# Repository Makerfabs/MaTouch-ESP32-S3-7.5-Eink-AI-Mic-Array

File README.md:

# MaTouch ESP32-S3 7.5 Eink AI Mic Array

## Introduction

Our MaTouch ESP32-S3 7.5-inch Quad-color E-Ink Display AI Microphone Array Development Board features a 7.5-inch quad-color e-paper display supporting black, white, red, and yellow color rendering. Based on microcapsule electrophoretic display technology, the screen drives charged pigment particles within microcapsules using electric fields, reflecting ambient light to form sharp images that deliver a natural reading experience similar to printed paper.
 
The board is powered by the ESP32-S3R8 main controller, equipped with 8 MB PSRAM and 16 MB SPI Flash. It integrates a four-microphone array and an ES7210 multi-channel audio ADC, enabling multi-channel audio capture for voice recognition, far-field sound pickup, and acoustic algorithm development. Additionally, it includes a QMI8658A six-axis inertial measurement unit providing accelerometer and gyroscope data for motion detection, orientation sensing, and interactive control. The board also features a camera, TF card slot, USB Type-C interface, lithium battery charging circuit, and reserved battery level monitoring functionality, making it ideal for application development in e-paper displays, image capture, voice interaction, and motion sensing.

Product Link: [MaTouch ESP32-S3 7.5 Eink AI Mic Array](https://www.makerfabs.com/matouch-esp32-s3-7-5-quad-color-eink-epaper.html)

Wiki Link:  [MaTouch ESP32-S3 7.5 Eink AI Mic Array](https://wiki.makerfabs.com/MaTouch%20ESP32_S3%207.5%20Eink%20AI%20Mic%20Array.html)

Example：1.[Camera_display_pic](https://github.com/Makerfabs/MaTouch-ESP32-S3-7.5-Eink-AI-Mic-Array#camera_display_pic)

2.[Voice_EPD_SD_Display](https://github.com/Makerfabs/MaTouch-ESP32-S3-7.5-Eink-AI-Mic-Array#voice_epd_sd_display)

## LCD Specs:

- PART NUMBER:KEGM075004E05
- SIZE:7.5 inch
- TYPE:Dot Matrix
- IC：JD79665
- RESOULUTION:800×480
- OUTLINE SIZE(mm):170.2×135.2×1.111
- ACTIVE SIZE(mm):163.2×97.92
- PIXEL PITCH(mm):0.204×0.204
- OPERATING TEMP:0°C ~ 40°C
- STORAGE TEMP:-25°C ~ 60°C
- CONNECTOR:24 Pin FPC
- COLOR:Black,White,Red,Yellow
- INTERFACE:SPI
- FULL REFRESH(S):20

## Features

- Controller:ESP32-S3
- Wireless:WiFi&Bluetooth 5.0
- Flash:16MB Flash
- PSRAM:8MB
- MICRO SD:Yes
- IMU:QMI8658A
- Camera:OV3660
- Microphone input:4-Microphone Array
- Audio ADC:ES7210
- USB:1*USB_NATIVE
- Arduino support:Yes

## Example

### Camera_display_pic

For details of this example, please refer to the [Wiki](https://wiki.makerfabs.com/MaTouch%20ESP32_S3%207.5%20Eink%20AI%20Mic%20Array.html#41-camera_display_pic) document.

### Voice_EPD_SD_Display

For details of this example, please refer to the [Wiki](https://wiki.makerfabs.com/MaTouch%20ESP32_S3%207.5%20Eink%20AI%20Mic%20Array.html#42-voice_epd_sd_display) document.

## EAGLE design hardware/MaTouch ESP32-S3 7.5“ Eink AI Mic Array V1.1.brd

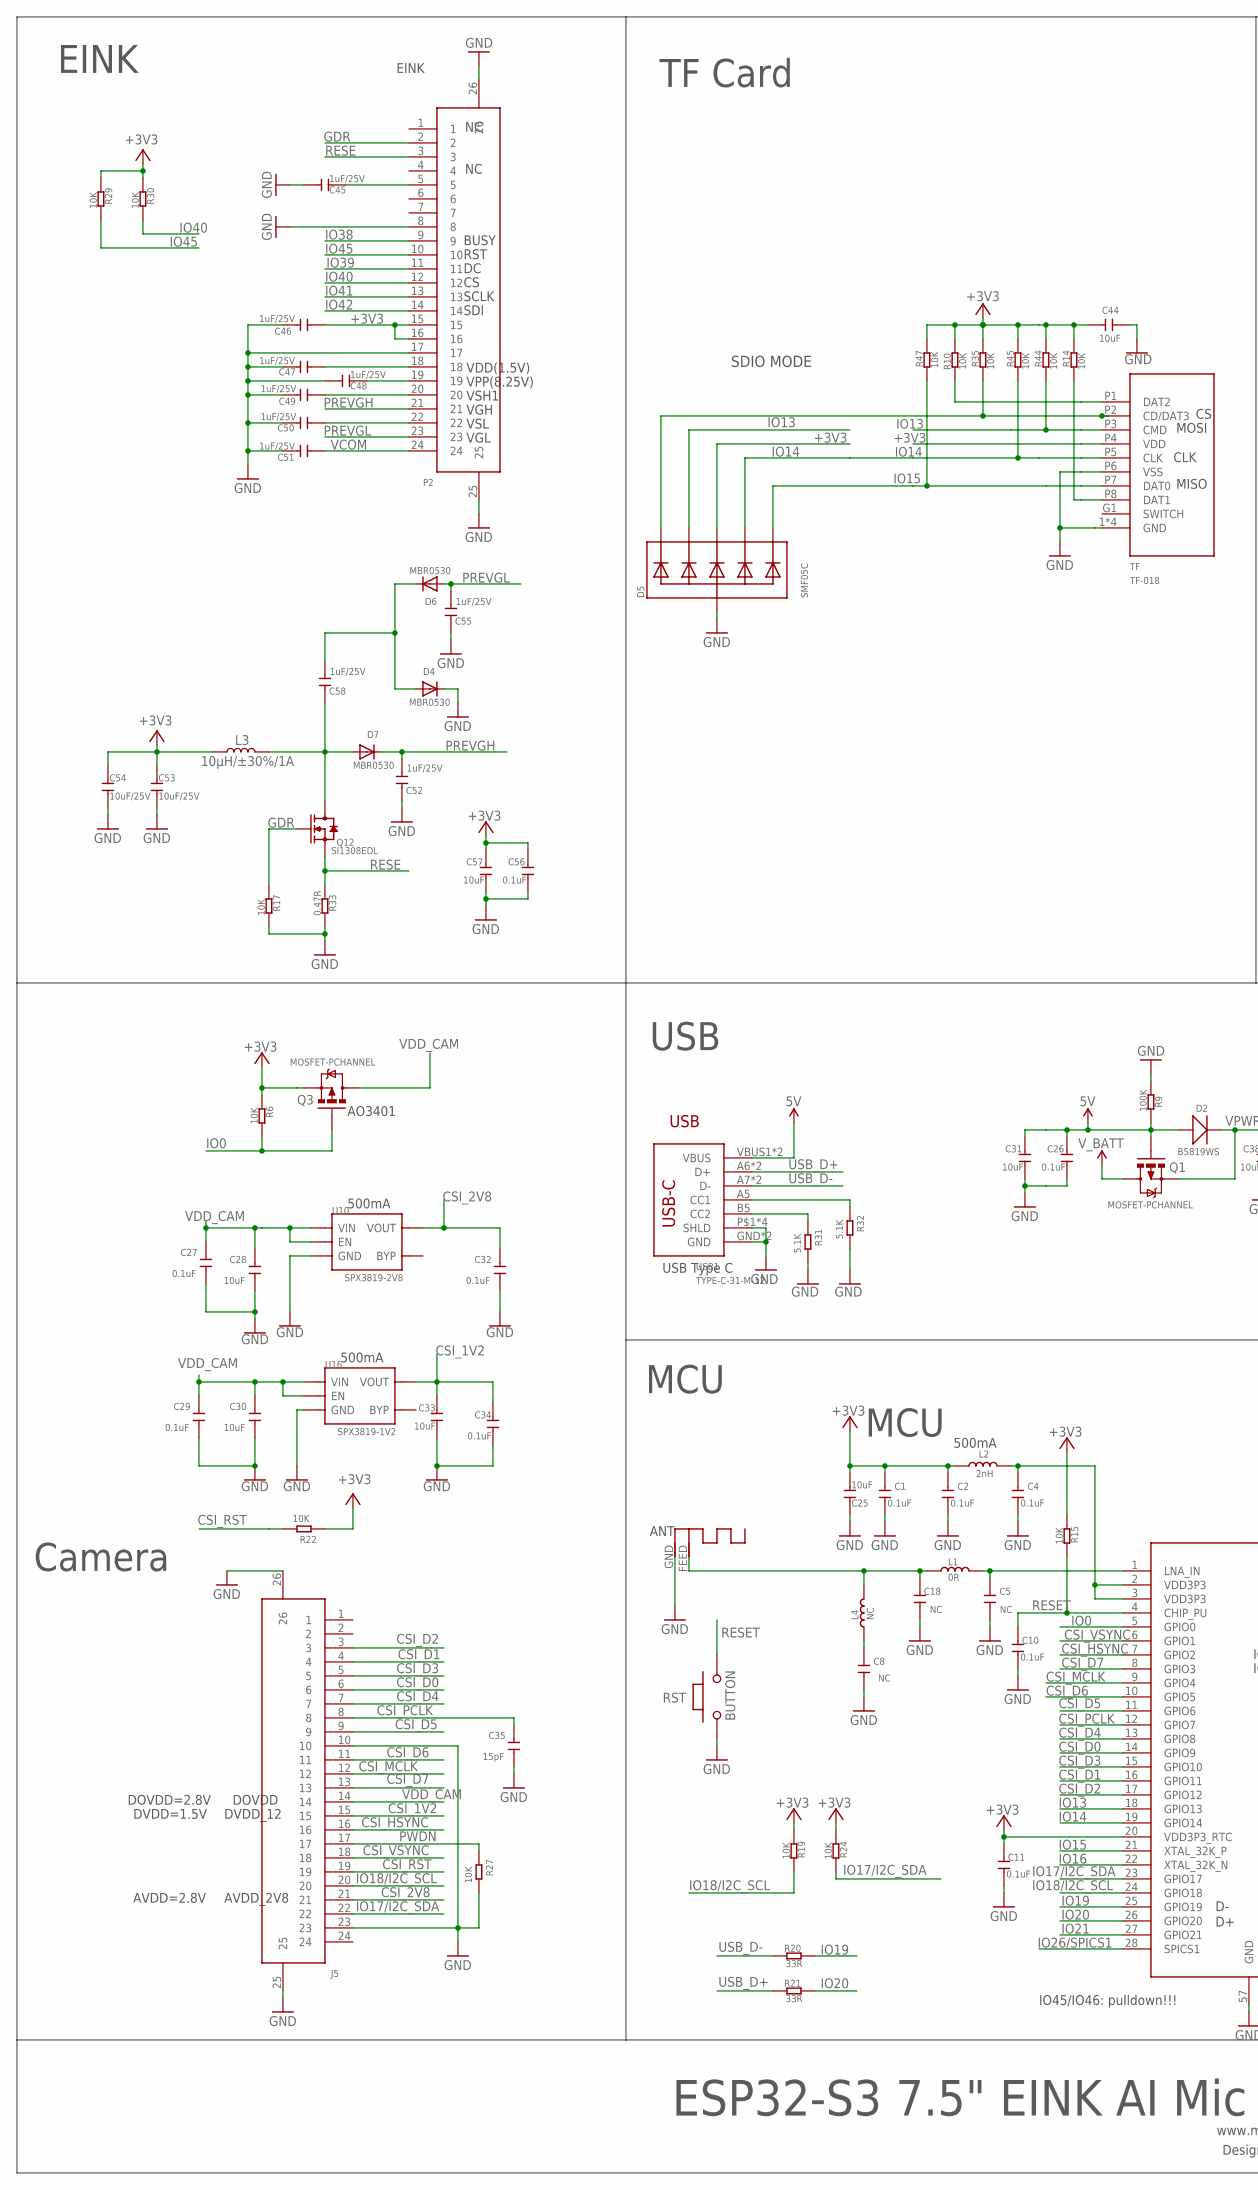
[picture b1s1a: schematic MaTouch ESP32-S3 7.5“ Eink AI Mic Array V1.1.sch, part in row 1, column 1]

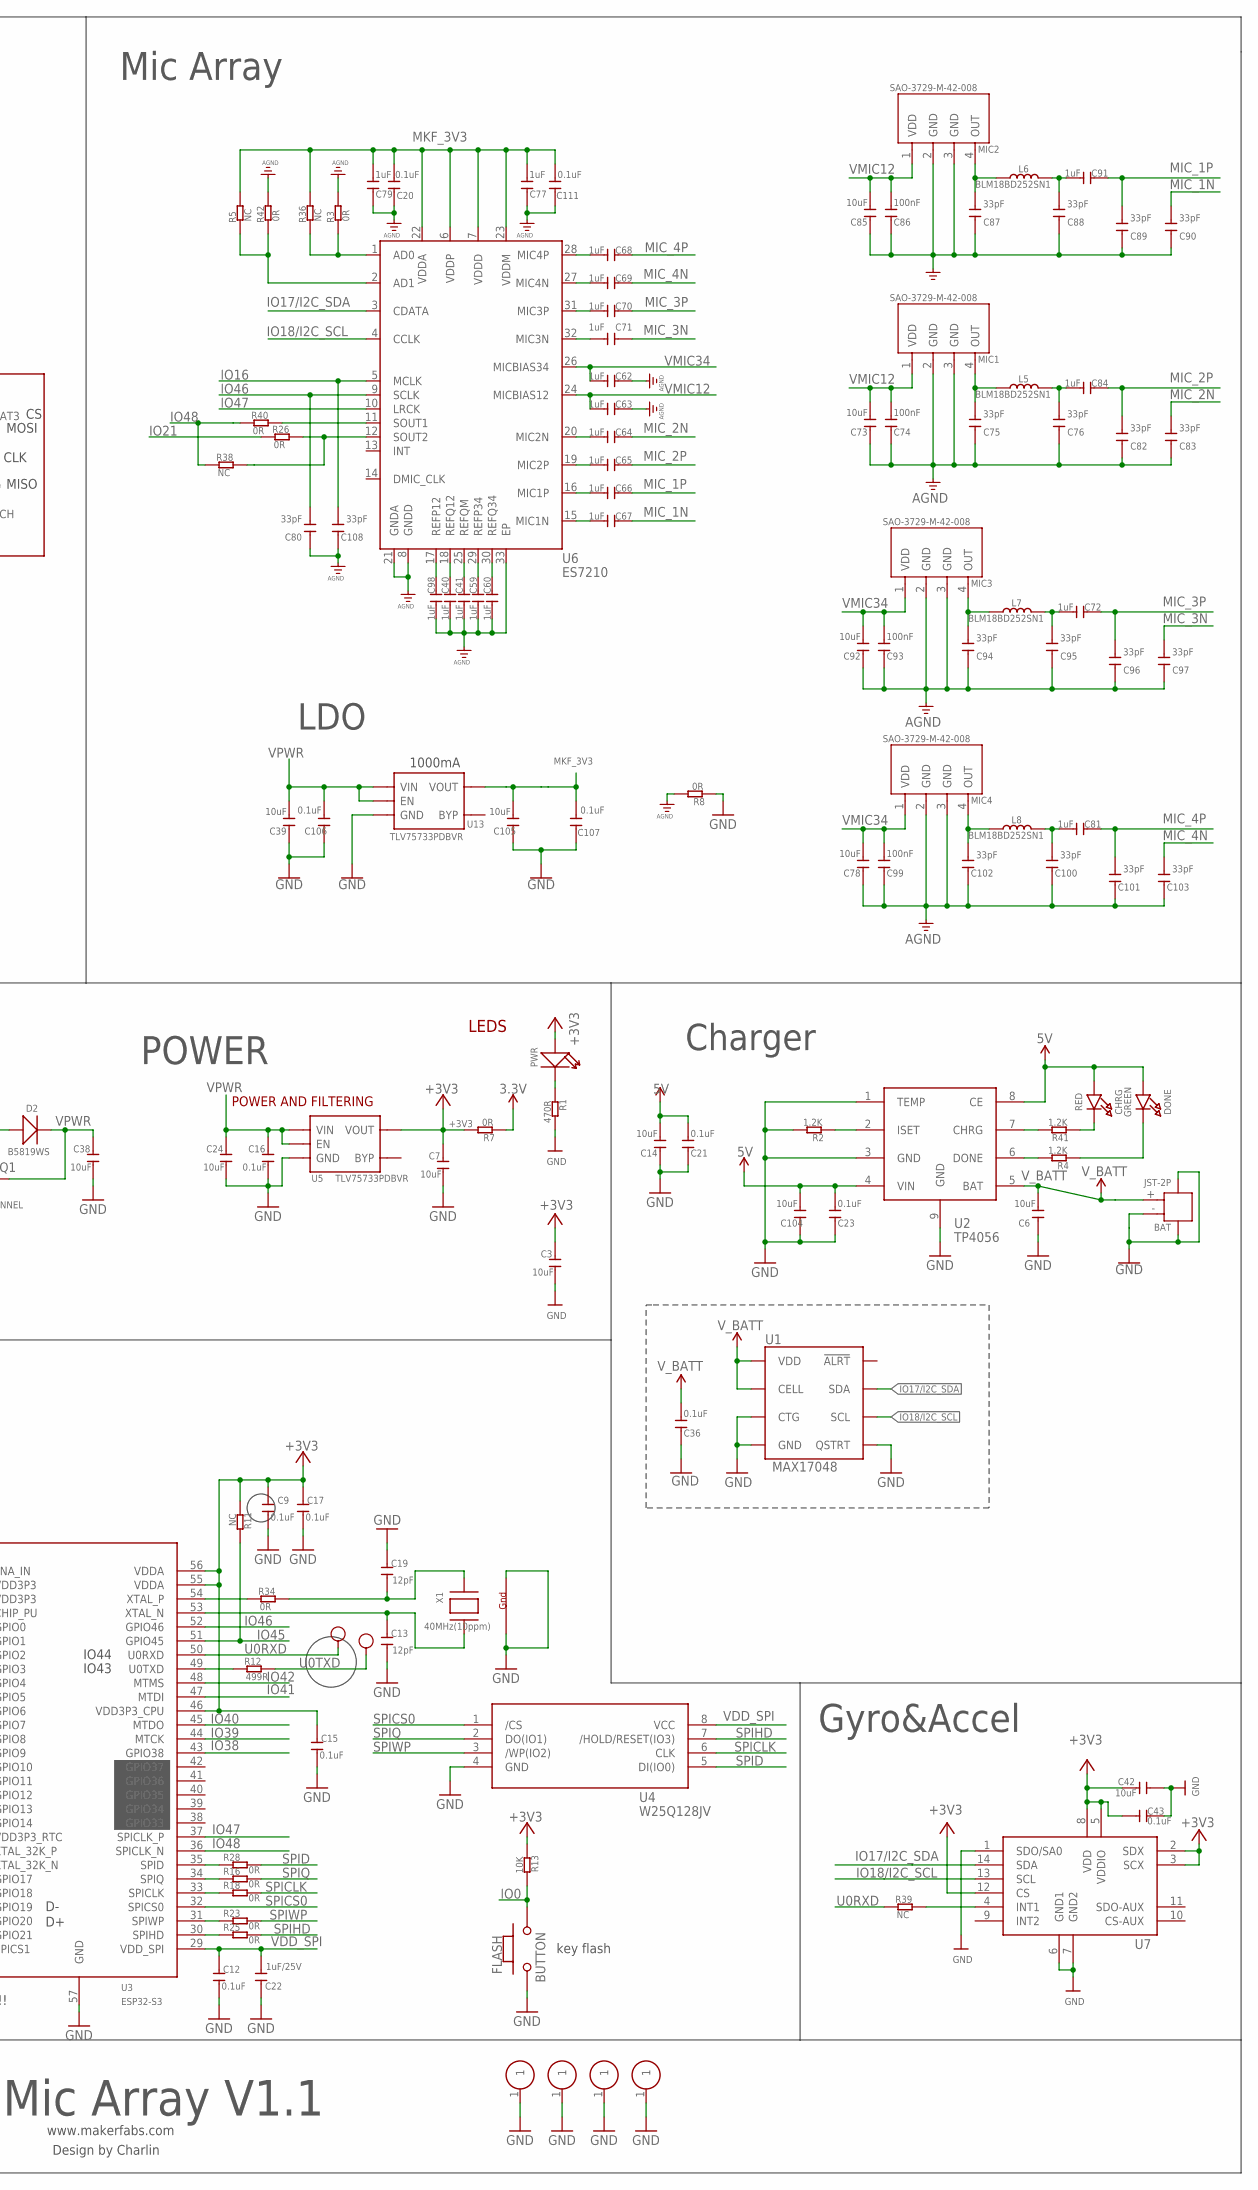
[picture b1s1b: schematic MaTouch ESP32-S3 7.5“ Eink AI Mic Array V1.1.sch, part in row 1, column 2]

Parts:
ANT1: ANTENNA; RN-ANT
BAT: JST-2P; HW2-SMD-2.0-90D
C1, C2, C4, C9, C10, C11, C12, C15, C16, C17, C20, C21, C23, C26, C27, C29, C32, C34, C36, C43, C56, C106, C107, C111: 0.1uF; DISCRETE_C0402
C3, C6, C7, C14, C24, C28, C30, C31, C33, C38, C39, C42, C44, C57, C73, C78, C85, C92, C104, C105: 10uF; DISCRETE_C0402
C5, C8, C18: NC; DISCRETE_C0402
C13, C19: 12pF; DISCRETE_C0402
C22, C45, C46, C47, C48, C49, C50, C51, C52, C55, C58: 1uF/25V; DISCRETE_C0402
C25: 10uF; DISCRETE_C0603
C35: 15pF; DISCRETE_C0402
C40, C41, C59, C60, C62, C63, C64, C65, C66, C67, C68, C69, C70, C71, C72, C77, C79, C81, C84, C91, C98: 1uF; DISCRETE_C0402
C53, C54: 10uF/25V; C0603
C74, C86, C93, C99: 100nF; DISCRETE_C0402
C75, C76, C80, C82, C83, C87, C88, C89, C90, C94, C95, C96, C97, C100, C101, C102, C103, C108: 33pF; DISCRETE_C0402
CHRG: RED; CHIPLED_0805_NOOUTLINE
D2: B5819WS; SOD323
D4, D6, D7: MBR0530; SOD-323F
D5: SMF05C; SOT363
DONE: GREEN; CHIPLED_0805_NOOUTLINE
FLASH: BUTTON; 157SW
J5: FPC-24P; SMD26-50P-1760L450W
L1: 0R; DISCRETE_L0402
L2: 2nH; DISCRETE_L0603
L3: 10µH/±30%/1A; CR54
L4: NC; DISCRETE_L0402
L5, L6, L7, L8: BLM18BD252SN1; L0603
MIC1, MIC2, MIC3, MIC4: SAO-3729-M-42-008; MIC4-SMD-3.76X2.95MM
P2: FPC-24P; SMD26-50P-1760L450W
PWR: DISCRETE_LED0603; DISCRETE_LED-0603
Q1, Q3: MOSFET-PCHANNEL; SOT23-3
Q12: SI1308EDL; SOT23
R1: 470R; DISCRETE_R0402
R2, R4, R41: 1.2K; DISCRETE_R0402
R3, R7, R8, R16, R18, R23, R25, R26, R28, R34, R40, R42: 0R; DISCRETE_R0402
R5, R11, R36, R38, R39: NC; DISCRETE_R0402
R6, R10, R13, R14, R15, R17, R19, R22, R24, R27, R29, R30, R35, R44, R45, R47: 10K; DISCRETE_R0402
R9: 100K; DISCRETE_R0402
R12: 499R; DISCRETE_R0402
R20, R21: 33R; DISCRETE_R0402
R31, R32: 5.1K; DISCRETE_R0402
R33: 0.47R; DISCRETE_R0402
RST: BUTTON; 157SW
RX: TEST-POINT'4545'; TP-D45MIL; PARTNO DNP
S1, S2, S3, S4: ONEPIN01
TF: TF-018
TX: TEST-POINT'4545'; TP-D45MIL; PARTNO DNP
U1: MAX17048; DFN-8
U2: TP4056; SOP8-1.27P
U3: ESP32-S3; QFN56-7*7MM
U4: W25Q128JV; SOIC-8-208MIL
U5, U13: TLV75733PDBVR; SOT23-5
U6: ES7210; QFN33-40P400L400W75H-280X280
U7: QMI8658A; LGA14-50P-300L250W86H
U10: SPX3819-2V8; SOT23-5
U16: SPX3819-1V2; SOT23-5
USB1: TYPE-C-31-M-12
X1: 40MHz(10ppm); NX3225

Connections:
3.3V: R7.2
5V: C14.1, C21.1, C23.1, C26.2, C31.2, C104.1, CHRG.A, D2.+, DONE.A, Q1.1 (G), R9.2, U2.4 (VIN), U2.8 (CE), USB1.VBUS1 (VBUS), USB1.VBUS2 (VBUS)
+3V3: C1.2, C2.2, C3.2, C7.2, C9.2, C11.2, C15.2, C17.2, C25.2, C42.2, C43.2, C44.2, C46.1, C53.1, C54.1, C56.2, C57.2, D5.4 (C3), L2.1, L3.P$1 (1), P2.15, P2.16, PWR.+, Q3.2 (S), R6.2, R7.1, R10.2, R11.2, R13.2, R14.2, R15.2, R19.2, R22.1, R24.2, R29.1, R30.1, R35.2, R44.2, R45.2, R47.2, TF.P4 (VDD), U3.20 (VDD3P3_RTC), U3.46 (VDD3P3_CPU), U3.55 (VDDA), U3.56 (VDDA), U5.5 (VOUT), U7.2 (SDX), U7.3 (SCX), U7.5 (VDDIO), U7.8 (VDD), U7.12 (CS)
AGND: C20.2, C40.2, C41.2, C59.2, C60.2, C62.1, C63.1, C73.2, C74.2, C75.2, C76.2, C77.2, C78.2, C79.2, C80.2, C82.2, C83.2, C85.2, C86.2, C87.2, C88.2, C89.2, C90.2, C92.2, C93.2, C94.2, C95.2, C96.2, C97.2, C98.2, C99.2, C100.2, C101.2, C102.2, C103.2, C108.2, C111.2, MIC1.2 (GND), MIC1.3 (GND), MIC2.2 (GND), MIC2.3 (GND), MIC3.2 (GND), MIC3.3 (GND), MIC4.2 (GND), MIC4.3 (GND), R3.1, R8.1, R42.1, U6.8 (GNDD), U6.21 (GNDA), U6.33 (EP)
CSI_1V2: C33.2, C34.2, J5.15, U16.5 (VOUT)
CSI_2V8: C32.2, J5.21, U10.5 (VOUT)
CSI_D0: J5.6, U3.14 (GPIO9)
CSI_D1: J5.4, U3.16 (GPIO11)
CSI_D2: J5.3, U3.17 (GPIO12)
CSI_D3: J5.5, U3.15 (GPIO10)
CSI_D4: J5.7, U3.13 (GPIO8)
CSI_D5: J5.9, U3.11 (GPIO6)
CSI_D6: J5.11, U3.10 (GPIO5)
CSI_D7: J5.13, U3.8 (GPIO3)
CSI_HSYNC: J5.16, U3.7 (GPIO2)
CSI_MCLK: J5.12, U3.9 (GPIO4)
CSI_PCLK: C35.2, J5.8, U3.12 (GPIO7)
CSI_RST: J5.19, R22.2
CSI_VSYNC: J5.18, U3.6 (GPIO1)
GDR: P2.2, Q12.1 (G), R17.1
GND: ANT1.GND, BAT.3, BAT.4, BAT.- (2), C1.1, C2.1, C3.1, C4.1, C5.1, C6.2, C7.1, C8.1, C9.1, C10.1, C11.1, C12.1, C13.1, C14.2, C15.1, C16.1, C17.1, C18.1, C19.2, C21.2, C22.2, C23.2, C24.1, C25.1, C26.1, C27.1, C28.1, C29.1, C30.1, C31.1, C32.1, C33.1, C34.1, C35.1, C36.2, C38.1, C39.2, C42.1, C43.1, C44.1, C45.2, C46.2, C47.2, C48.2, C49.2, C50.2, C51.2, C52.2, C53.2, C54.2, C55.2, C56.1, C57.1, C104.2, C105.2, C106.2, C107.2, D4.C, D5.2 (A), FLASH.1, J5.10, J5.23, J5.25, J5.26, P2.8, P2.17, P2.25, P2.26, R1.1, R2.1, R8.2, R9.1, R17.2, R27.2, R31.2, R32.2, R33.2, RST.1, S1.1, S2.1, S3.1, S4.1, TF.1 (GND), TF.2 (GND), TF.3 (GND), TF.4 (GND), TF.P6 (VSS), U1.1 (CTG), U1.4 (GND), U1.6 (QSTRT), U1.9 (GND), U2.1 (TEMP), U2.3 (GND), U2.9 (GND), U3.57 (GND), U4.4 (GND), U5.2 (GND), U7.1 (SDO/SA0), U7.6 (GND1), U7.7 (GND2), U10.2 (GND), U13.2 (GND), U16.2 (GND), USB1.GND, USB1.GND2 (GND), USB1.P$1 (SHLD), USB1.P$2 (SHLD), USB1.P$3 (SHLD), USB1.P$4 (SHLD), X1.2 (G2), X1.4 (G1)
IO0: FLASH.2, Q3.1 (G), R6.1, R13.1, U3.5 (GPIO0)
IO13: D5.3 (C2), R44.1, TF.P3 (CMD), U3.18 (GPIO13)
IO14: D5.5 (C4), R45.1, TF.P5 (CLK), U3.19 (GPIO14)
IO15: D5.6 (C5), R47.1, TF.P7 (DAT0), U3.21 (XTAL_32K_P)
IO16: C108.1, U3.22 (XTAL_32K_N), U6.5 (MCLK)
IO17/I2C_SDA: J5.22, R24.1, U1.8 (SDA), U3.23 (GPIO17), U6.3 (CDATA), U7.14 (SDA)
IO18/I2C_SCL: J5.20, R19.1, U1.7 (SCL), U3.24 (GPIO18), U6.4 (CCLK), U7.13 (SCL)
IO19: R20.1, U3.25 (GPIO19)
IO20: R21.1, U3.26 (GPIO20)
IO21: R26.2, U3.27 (GPIO21)
IO26/SPICS1: U3.28 (SPICS1)
IO38: P2.9, U3.43 (GPIO38)
IO39: P2.11, U3.44 (MTCK)
IO40: P2.12, R30.2, U3.45 (MTDO)
IO41: P2.13, U3.47 (MTDI)
IO42: P2.14, U3.48 (MTMS)
IO45: P2.10, R11.1, R29.2, U3.51 (GPIO45)
IO46: C80.1, U3.52 (GPIO46), U6.9 (SCLK)
IO47: U3.37 (SPICLK_P), U6.10 (LRCK)
IO48: R38.2, R40.2, U3.36 (SPICLK_N)
MIC_1N: C67.1, C90.1
MIC_1P: C66.1, C89.1, C91.1
MIC_2N: C64.1, C83.1
MIC_2P: C65.1, C82.1, C84.1
MIC_3N: C71.1, C97.1
MIC_3P: C70.1, C72.1, C96.1
MIC_4N: C69.1, C103.1
MIC_4P: C68.1, C81.1, C101.1
MKF_3V3: C20.1, C77.1, C79.1, C105.1, C107.1, C111.1, R5.1, R36.1, U6.6 (VDDP), U6.7 (VDDD), U6.22 (VDDA), U6.23 (VDDM), U13.5 (VOUT)
unnamed: ANT1.FEED, C18.2, L1.1, L4.2
unnamed: C5.2, L1.2, U3.1 (LNA_IN)
unnamed: R28.2, U3.35 (SPID)
unnamed: C8.2, L4.1
unnamed: R32.1, USB1.A5 (CC1)
unnamed: C45.1, P2.5
unnamed: PWR.-, R1.2
unnamed: C48.1, P2.19
unnamed: C49.1, P2.20
unnamed: C50.1, P2.22
unnamed: C58.1, D4.A, D6.C
unnamed: R2.2, U2.2 (ISET)
unnamed: R41.1, U2.7 (CHRG)
unnamed: R4.1, U2.6 (DONE)
unnamed: CHRG.C, R41.2
unnamed: DONE.C, R4.2
unnamed: C98.1, U6.17 (REFP12)
unnamed: C40.1, U6.18 (REFQ12)
unnamed: C41.1, U6.25 (REFQM)
unnamed: C59.1, U6.29 (REFP34)
unnamed: R10.1, TF.P1 (DAT2)
unnamed: C47.1, P2.18
unnamed: C60.1, U6.30 (REFQ34)
unnamed: C67.2, U6.15 (MIC1N)
unnamed: C66.2, U6.16 (MIC1P)
unnamed: C64.2, U6.20 (MIC2N)
unnamed: C70.2, U6.31 (MIC3P)
unnamed: R14.1, TF.P8 (DAT1)
unnamed: D5.1 (C1), R35.1, TF.P2 (CD/DAT3)
unnamed: C65.2, U6.19 (MIC2P)
unnamed: C76.1, C84.2, L5.2
unnamed: R3.2, R36.2, U6.1 (AD0)
unnamed: C4.2, L2.2, U3.2 (VDD3P3), U3.3 (VDD3P3)
unnamed: R31.1, USB1.B5 (CC2)
unnamed: R16.2, U3.34 (SPIQ)
unnamed: R40.1, U6.11 (SOUT1)
unnamed: R34.2, U3.54 (XTAL_P)
unnamed: R18.2, U3.33 (SPICLK)
unnamed: C71.2, U6.32 (MIC3N)
unnamed: R23.2, U3.31 (SPIWP)
unnamed: R25.2, U3.30 (SPIHD)
unnamed: R39.1, U7.4 (INT1)
unnamed: C75.1, L5.1, MIC1.4 (OUT)
unnamed: C88.1, C91.2, L6.2
unnamed: C87.1, L6.1, MIC2.4 (OUT)
unnamed: C69.2, U6.27 (MIC4N)
unnamed: C81.2, C100.1, L8.2
unnamed: C72.2, C95.1, L7.2
unnamed: C68.2, U6.28 (MIC4P)
unnamed: R26.1, R38.1, U6.12 (SOUT2)
unnamed: C94.1, L7.1, MIC3.4 (OUT)
unnamed: R5.2, R42.2, U6.2 (AD1)
unnamed: R12.2, U3.49 (U0TXD)
unnamed: C13.2, U3.53 (XTAL_N), X1.3 (X2)
unnamed: C19.1, R34.1, X1.1 (X1)
unnamed: C102.1, L8.1, MIC4.4 (OUT)
unnamed: C58.2, D7.A, L3.P$2 (2), Q12.3 (D)
PREVGH: C52.1, D7.C, P2.21
PREVGL: C55.1, D6.A, P2.23
PWDN: J5.17, R27.1
RESE: P2.3, Q12.2 (S), R33.1
RESET: C10.2, R15.1, RST.2, U3.4 (CHIP_PU)
SPICLK: R18.1, U4.6 (CLK)
SPICS0: U3.32 (SPICS0), U4.1 (/CS)
SPID: R28.1, U4.5 (DI(IO0))
SPIHD: R25.1, U4.7 (/HOLD/RESET(IO3))
SPIQ: R16.1, U4.2 (DO(IO1))
SPIWP: R23.1, U4.3 (/WP(IO2))
U0RXD: R39.2, RX.T, U3.50 (U0RXD)
U0TXD: R12.1, TX.T
USB_D+: R21.2, USB1.A6 (D+), USB1.B6 (D+)
USB_D-: R20.2, USB1.A7 (D-), USB1.B7 (D-)
VCOM: C51.1, P2.24
VDD_CAM: C27.2, C28.2, C29.2, C30.2, J5.14, Q3.3 (D), U10.1 (VIN), U10.3 (EN), U16.1 (VIN), U16.3 (EN)
VDD_SPI: C12.2, C22.1, U3.29 (VDD_SPI), U4.8 (VCC)
VMIC12: C63.2, C73.1, C74.1, C85.1, C86.1, MIC1.1 (VDD), MIC2.1 (VDD), U6.24 (MICBIAS12)
VMIC34: C62.2, C78.1, C92.1, C93.1, C99.1, MIC3.1 (VDD), MIC4.1 (VDD), U6.26 (MICBIAS34)
VPWR: C16.2, C24.2, C38.2, C39.1, C106.1, D2.-, Q1.2 (S), U5.1 (VIN), U5.3 (EN), U13.1 (VIN), U13.3 (EN)
V_BATT: BAT.+ (1), C6.1, C36.1, Q1.3 (D), U1.2 (CELL), U1.3 (VDD), U2.5 (BAT)

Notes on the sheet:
www.makerfabs.com
Design by Charlin
LEDS
POWER AND FILTERING
key flash
ESP32-S3 7.5" EINK AI Mic Array V1.1
POWER
MCU
500mA
IO45/IO46: pulldown!!!
IO43
IO44
ANT
USB
DVDD=1.5V
AVDD=2.8V
DOVDD=2.8V
Camera
AVDD_2V8
DVDD_12
DOVDD
USB Type C
AO3401
Gyro&Accel
SDIO MODE
TF Card
MOSI
CLK
MISO
EINK
VDD(1.5V)
VPP(8.25V)
VSH1
VGH
VSL
VGL
BUSY
RST
SCLK
SDI

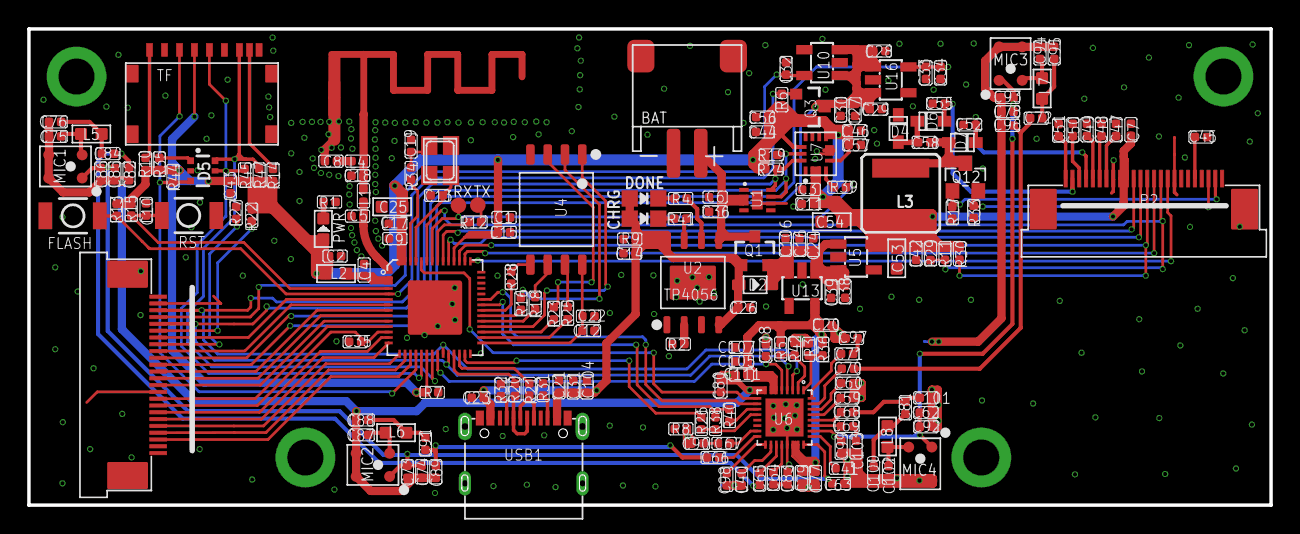
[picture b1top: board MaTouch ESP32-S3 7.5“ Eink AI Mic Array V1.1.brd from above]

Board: 2 copper layers, 91.3 x 35.0 mm, 200 parts (1 on the bottom side), 127 nets.

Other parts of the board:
U$1: MAKERFABS_0.3

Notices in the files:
parts and their libraries:
User-Submitted: Licensing: Creative Commons ShareAlike 4.0 International - https://creativecommons.org/licenses/by-sa/4.0
microbuilder: This work is placed in the public domain, and may be freely used for commercial and non-commercial work with the following conditions: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
